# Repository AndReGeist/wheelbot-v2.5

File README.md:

# wheelbot-v2.5

This repository contains all files required to build a Wheelbot v2.5.

Project page:  [https://sites.google.com/view/wheelbot/start](https://sites.google.com/view/wheelbot/start)

## [/CAD files](https://github.com/AndReGeist/wheelbot-v2.5/tree/main/CAD%20files)
Contains the CAD files of the Wheelbot v2.5 as stl-files.

3D printer used: Markforged Onyx One <br/>
Material: Onyx <br/>
Layer height: 0.2 mm <br/>
Use default settings for all else. <br/>
See the following links for tips on printing: <br/>
https://markforged.com/resources/learn/design-for-additive-manufacturing-plastics-composites/3d-printing-strategies-for-composites/composites-3d-printing-design-tips <br/>
https://static.markforged.com/downloads/CompositesDesignGuide.pdf

The folder also contains the technical drawing for the cut copper rings forming the reaction wheel and the pdf *"wheelbot v2.5 assembly view.pdf"* that lets you interact with the complete Wheelbot's assembly (requires Adobe Acrobate reader).

## [/motherboard circuitry](https://github.com/AndReGeist/wheelbot-v2.5/tree/main/motherboard%20circuitry)
Contains the circuit layouts of the motherboard that connects to the Maevarm M2 and which also supplies the uDriver-v2 with power.

## [/simulation/matlab-symbolic-derivation-EOM](https://github.com/AndReGeist/wheelbot-v2.5/tree/main/simulation/matlab-symbolic-derivation-EOM)
Contains the matlab files used to symbolically derive the EOM of the Wheelbot.

**FlywUni_symbolic_derive.m:** Derives the Euler-Lagrange equations of a unicycle reaction wheel robot using the parameters set in "config_FlyUni" and the "Langrange.m" defined in external libraries.

**FlywUni_symbolic_linearize.m:** Reshapes the symbolic ODE obtained from "FlywUni_symbolic_derive", brings it into the form for the standard matlab ODE solvers and saves it as 
```matlab
save('EQS_matrices_nonlin.mat', 'M_nonlin', 'RHS_nonlin')
```
Also linearizes the set of equations and saves the linearization as 
```matlab
save('EQS_matrices.mat', 'M', 'RHS')
```

**FlywUni_symbolic_analyze.m:** Loads the pre-computed dynamic equations, computes a trajectory using a standard ODE solver (RK45), and plots trajectory and total energy of the system.

## [/simulation/simulink-model](https://github.com/AndReGeist/wheelbot-v2.5/tree/main/simulation/simulink-model)
Contains the simulink model used to tune the estimator and LQR controller. Recommended matlab version is R2020a.

The file *"s00_config"* contains the simulation settings including the exact estimates for the mass and inertia of the Wheelbot v2.5 which we obtained from CAD.

Before running *"s01_unicycle.slx"*, you need to run *"s00_designLQR"*.

## [/firmware](https://github.com/AndReGeist/wheelbot-v2.5/tree/main/firmware)
Contains the firmware required to run Wheelbot v2.5

### /firmware/M2-on-wheelbot
Contains the firmware that runs on a Maevarm M2 that is attached to the motherboard of the Wheelbot.

### /firmware/M2-wifi-dongle
Contains the firmware that runs on a Maevarm M2 being connected to a PC and that handles the wifi communication with the Wheelbot.

### /firmware/computer-python-interface
Python program running on Ubuntu 18.04 LTS collecting incoming data/outgoing commands from/to the wifi dongle.

# Erratum
In the initial publication, in Equation (3), the transform from averaged body rates ${}^{\text{B}}\omega_i$ to Euler rates was incorrectly denoted as

```math
\begin{bmatrix}
\dot{q}_{1, \mathrm{G}} \\
\dot{q}_{2, \mathrm{G}} \\
\dot{q}_{3, \mathrm{G}}
\end{bmatrix} = \begin{bmatrix}
e_1^{\mathrm{T}} R_2 \\
e_2^{\mathrm{T}} \\
e_3^{\mathrm{T}} R_1 R_2
\end{bmatrix} \sum_{k=1}^4 \frac{{ }^B \omega_i(k)}{4},
```

corresponding to

```math
\left[\begin{array}{c}
\dot{q}_{1, \mathrm{G}} \\
\dot{q}_{2, \mathrm{G}} \\
\dot{q}_{3, \mathrm{G}}
\end{array}\right]=\left[\begin{array}{c}
R_2^T e_1 &
e_2 &
R_2^T R_1^T e_3
\end{array}\right]^{\top} \sum_{i=1}^4 \frac{{ }^B \omega_i(k)}{4}.
```

However, the correct transform from averaged body rates ${}^{\text{B}}\omega_i$ to Euler rates is

```math
\left[\begin{array}{c}
\dot{q}_{1, \mathrm{G}} \\
\dot{q}_{2, \mathrm{G}} \\
\dot{q}_{3, \mathrm{G}}
\end{array}\right]=\left[\begin{array}{c}
R_2^T e_1 &
e_2 &
R_2^T R_1^T e_3
\end{array}\right]^{-1} \sum_{i=1}^4 \frac{{ }^B \omega_i(k)}{4}.
```

While we implemented the faulty transform in the Wheelbot's state estimation routine (see [main.c](https://github.com/AndReGeist/wheelbot-v2.5/blob/main/firmware/M2-on-wheelbot/src/main.c), Line 340),  the error had not been noticed during experimentation as the robot remained close to its upright equilibrium. In turn, $q_1$ and $q_2$ remained near zero such that both transforms became almost identical, as

```math
\left[\begin{array}{c}
R_2^T e_1 &
e_2 &
R_2^T R_1^T e_3
\end{array}\right]^{\top} =  \left[\begin{array}{c}
\cos(q_2) & 0 & \sin(q_2) \\
0 & 1 & 0 \\
-\cos(q_1) \sin(q_2) & \sin(q_1) & \cos(q_1) \cos(q_2)
\end{array}\right],
```

```math
\left[\begin{array}{c}
R_2^T e_1 &
e_2 &
R_2^T R_1^T e_3
\end{array}\right]^{-1} = \left[\begin{array}{c}
 \cos(q_2) & 0 & \sin(q_2) \\
 \tan(q_1) \sin(q_2) & 1 & -\tan(q_1) \cos(q_2) \\ 
 -\sin(q_2) / \cos(q_1) & 0 & \cos(q_2) / \cos(q_1)
\end{array}\right].
```

Importantly, **our results on tilt estimation using accelerometers** as depicted in Figure 10 **are not affected by this error**. In the first experiment (Figure 10, left) the robot's tilt angles were kept at zero. In the second experiment (Figure 10, right), $q_1 \approx 0$ such that $\tan(q_1) \approx q_1$. In turn, both transforms deviated only marginally from each other in both experiments.

We added a [Jupyter notebook](https://github.com/AndReGeist/wheelbot-v2.5/blob/main/erratum_bodyrate_transform.ipynb) to the projects Github repository detailing the calculation of the transform from body rates to Euler rates.

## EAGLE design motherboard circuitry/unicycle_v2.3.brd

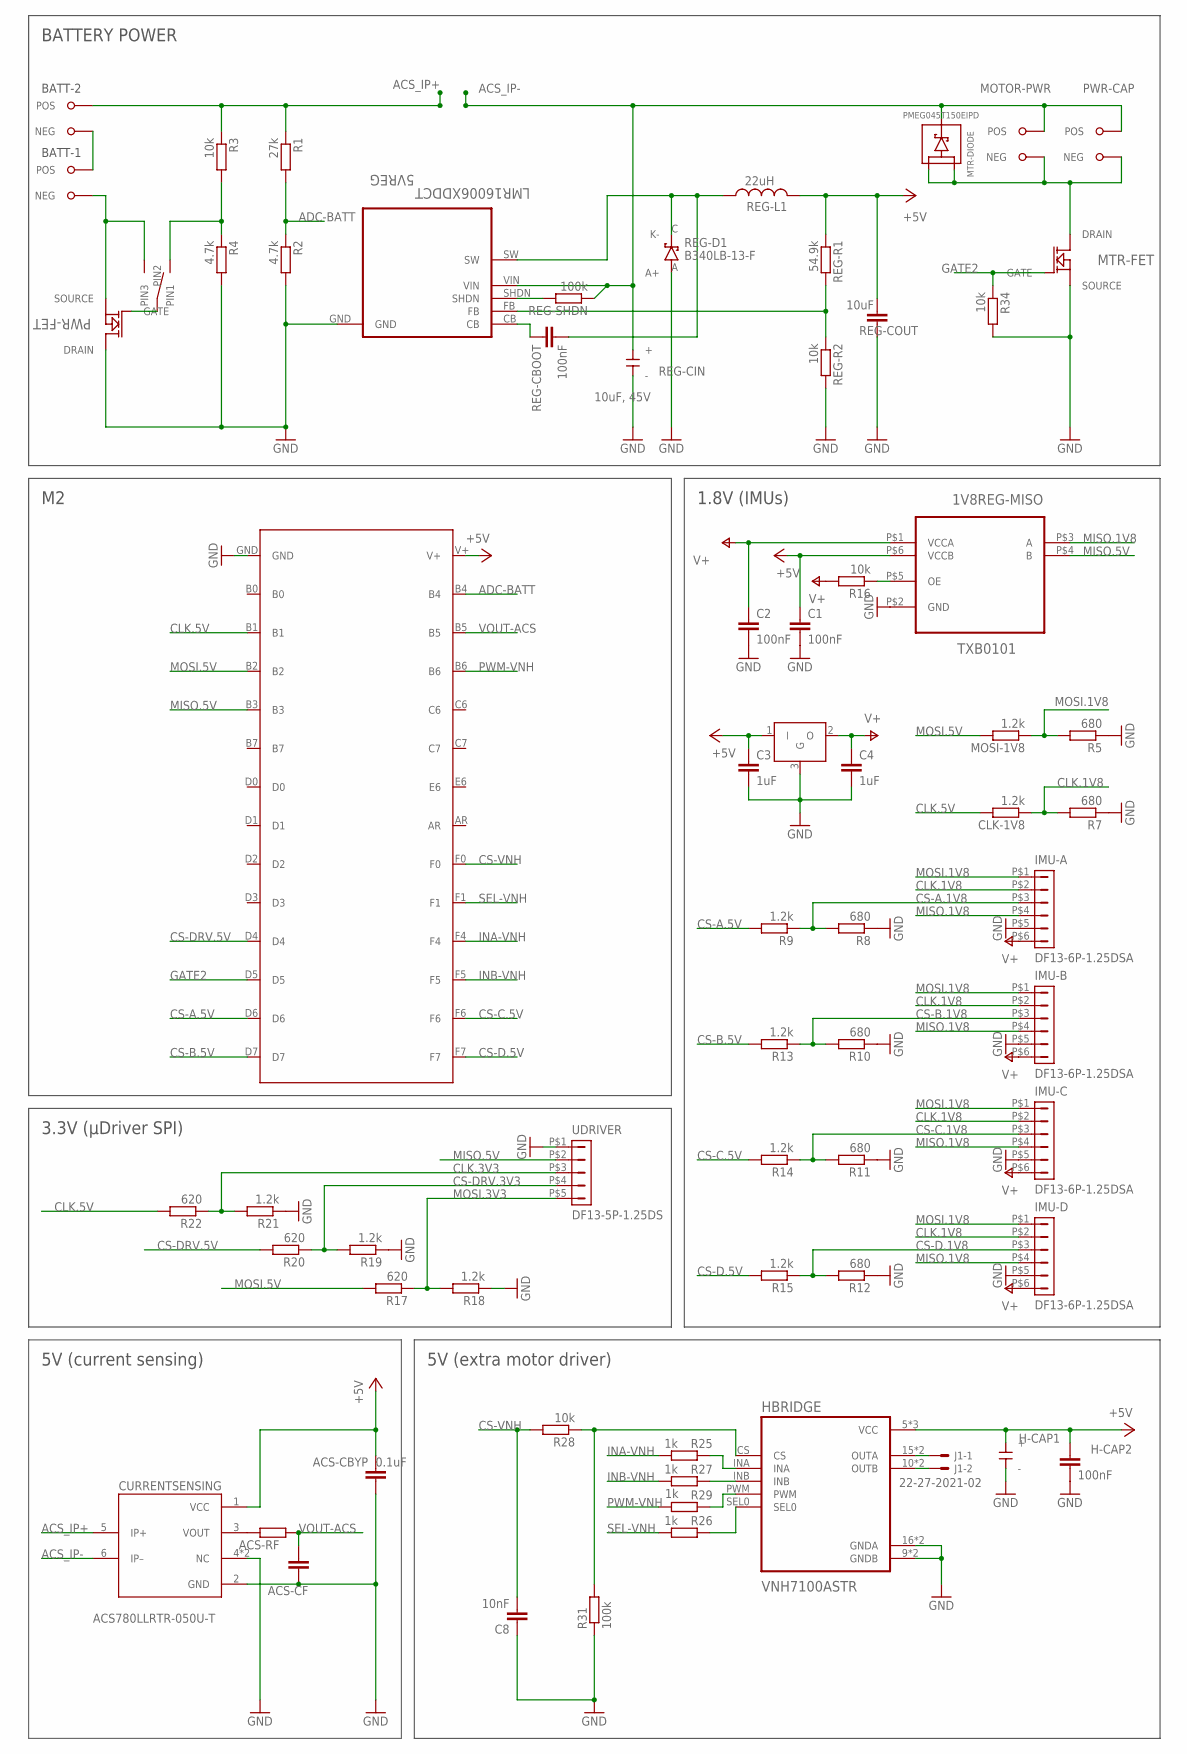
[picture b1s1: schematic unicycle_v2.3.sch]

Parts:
1V8-REG: AP7333AG; SOT23
1V8REG-MISO: TXB0101; SOT23-6
5VREG: LMR16006XDDCT; SOT95P280X110-6N
ACS-CBYP: 0.1uF; C0603
ACS-CF: C-EUC0603; C0603
ACS-RF: R-EU_R0603; R0603
C1, C2: 100nF; C0402
C3, C4: 1uF; C0402
C8: 10nF; C0402
CLK-1V8: 1.2k; R0402
CURRENTSENSING: ACS780LLRTR-050U-T; XDCR_ACS780LLRTR-050B-T
H-CAP1: TPSD337K006R0045; AVX_TPS-D
H-CAP2: 100nF; C0402
HBRIDGE: VNH7100ASTR; SOIC127P600X175-16N
IMU-A: DF13-6P-1.25DSA
IMU-B: DF13-6P-1.25DSA
IMU-C: DF13-6P-1.25DSA
IMU-D: DF13-6P-1.25DSA
J1: 22-27-2021-02; 6410-02
MOSI-1V8: 1.2k; R0402
MOTOR-PWR: 21AWG_X2
MTR-DIODE: PMEG045T150EIPD
MTR-FET: CSD18540Q5BT; DNK0008A
PWR-CAP: 21AWG_X2
PWR-FET: CSD18540Q5BT; DNK0008A
R1: 27k; R0402
R2, R4: 4.7k; R0402
R3, R16, R28, R34: 10k; R0402
R5, R7, R8, R10, R11, R12: 680; R0402
R9, R13, R14, R15, R18, R19, R21: 1.2k; R0402
R17, R20, R22: 620; R0402
R25, R26, R27, R29: 1k; R0402
R31: 100k; R0402
REG-CBOOT: 100nF; C0402
REG-CIN: 10uF, 45V; TCJD106M050R0120
REG-COUT: 10uF; C0603
REG-D1: B340LB-13-F; DIODES-SMB
REG-L1: 22uH; 4020
REG-R1: 54.9k; R0402
REG-R2: 10k; R0402
REG-SHDN: 100k; R0402
SWITCH: ATE1D-2M3-10-Z
U$2: M2; M1
U$8, U$9: XT30PW-M; XT30PW-M-NOHOLE
UDRIVER: DF13-5P-1.25DS

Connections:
+5V: 1V8-REG.1 (I), 1V8REG-MISO.P$6 (VCCB), ACS-CBYP.2, C1.1, C3.1, CURRENTSENSING.1 (VCC), H-CAP1.POS (+), H-CAP2.1, HBRIDGE.5 (VCC), HBRIDGE.12 (VCC), HBRIDGE.VCC, REG-COUT.1, REG-L1.P$2 (2), REG-R1.1, U$2.V+
ACS_IP+: CURRENTSENSING.5 (IP+), R1.1, R3.1, U$8.POS
ACS_IP-: 5VREG.VIN, CURRENTSENSING.6 (IP–), MOTOR-PWR.POS, MTR-DIODE.3 (K), PWR-CAP.POS, REG-CIN.POS (+), REG-SHDN.1
ADC-BATT: R1.2, R2.1, U$2.B4
CLK.1V8: CLK-1V8.1, IMU-A.P$2 (2), IMU-B.P$2 (2), IMU-C.P$2 (2), IMU-D.P$2 (2), R7.2
CLK.3V3: R21.2, R22.1, UDRIVER.P$3 (3)
CLK.5V: CLK-1V8.2, R22.2, U$2.B1
CS-A.1V8: IMU-A.P$3 (3), R8.2, R9.1
CS-A.5V: R9.2, U$2.D6
CS-B.1V8: IMU-B.P$3 (3), R10.2, R13.1
CS-B.5V: R13.2, U$2.D7
CS-C.1V8: IMU-C.P$3 (3), R11.2, R14.1
CS-C.5V: R14.2, U$2.F6
CS-D.1V8: IMU-D.P$3 (3), R12.2, R15.1
CS-D.5V: R15.2, U$2.F7
CS-DRV.3V3: R19.2, R20.1, UDRIVER.P$4 (4)
CS-DRV.5V: R20.2, U$2.D4
CS-VNH: C8.2, R28.2, U$2.F0
GATE2: MTR-FET.4 (GATE), R34.1, U$2.D5
GND: 1V8-REG.3 (G), 1V8REG-MISO.P$2 (GND), 5VREG.GND, ACS-CBYP.1, ACS-CF.2, C1.2, C2.2, C3.2, C4.2, C8.1, CURRENTSENSING.2 (GND), CURRENTSENSING.4 (NC), CURRENTSENSING.7 (NC), H-CAP1.NEG (-), H-CAP2.2, HBRIDGE.9 (GNDB), HBRIDGE.16 (GNDA), HBRIDGE.GNDA, HBRIDGE.GNDB, IMU-A.P$5 (5), IMU-B.P$5 (5), IMU-C.P$5 (5), IMU-D.P$5 (5), MTR-FET.1 (SOURCE), MTR-FET.2 (SOURCE), MTR-FET.3 (SOURCE), PWR-FET.9 (DRAIN), R2.2, R4.2, R5.1, R7.1, R8.1, R10.1, R11.1, R12.1, R18.1, R19.1, R21.1, R31.1, R34.2, REG-CIN.NEG (-), REG-COUT.2, REG-D1.A (A+), REG-R2.2, U$2.GND, UDRIVER.P$1 (1)
INA-VNH: R25.2, U$2.F4
INB-VNH: R27.2, U$2.F5
MISO.1V8: 1V8REG-MISO.P$3 (A), IMU-A.P$4 (4), IMU-B.P$4 (4), IMU-C.P$4 (4), IMU-D.P$4 (4)
MISO.5V: 1V8REG-MISO.P$4 (B), U$2.B3, UDRIVER.P$2 (2)
MOSI.1V8: IMU-A.P$1 (1), IMU-B.P$1 (1), IMU-C.P$1 (1), IMU-D.P$1 (1), MOSI-1V8.1, R5.2
MOSI.3V3: R17.1, R18.2, UDRIVER.P$5 (5)
MOSI.5V: MOSI-1V8.2, R17.2, U$2.B2
unnamed: 5VREG.SHDN, REG-SHDN.2
unnamed: HBRIDGE.15 (OUTA), HBRIDGE.OUTA, J1.1
unnamed: MOTOR-PWR.NEG, MTR-DIODE.1 (A1), MTR-DIODE.2 (A2), MTR-FET.9 (DRAIN), PWR-CAP.NEG
unnamed: 5VREG.FB, REG-R1.2, REG-R2.1
unnamed: 5VREG.SW, REG-CBOOT.1, REG-D1.C (K-), REG-L1.P$1 (1)
unnamed: 5VREG.CB, REG-CBOOT.2
unnamed: 1V8REG-MISO.P$5 (OE), R16.1
unnamed: U$8.NEG, U$9.POS
unnamed: PWR-FET.1 (SOURCE), PWR-FET.2 (SOURCE), PWR-FET.3 (SOURCE), SWITCH.P$3 (PIN3), U$9.NEG
unnamed: R3.2, R4.1, SWITCH.P$1 (PIN1)
unnamed: HBRIDGE.INB, R27.1
unnamed: HBRIDGE.SEL0, R26.1
unnamed: HBRIDGE.PWM, R29.1
unnamed: PWR-FET.4 (GATE), SWITCH.P$2 (PIN2)
unnamed: HBRIDGE.CS, R28.1, R31.2
unnamed: ACS-RF.2, CURRENTSENSING.3 (VOUT)
unnamed: HBRIDGE.10 (OUTB), HBRIDGE.OUTB, J1.2
unnamed: HBRIDGE.INA, R25.1
PWM-VNH: R29.2, U$2.B6
SEL-VNH: R26.2, U$2.F1
V+: 1V8-REG.2 (O), 1V8REG-MISO.P$1 (VCCA), C2.1, C4.1, IMU-A.P$6 (6), IMU-B.P$6 (6), IMU-C.P$6 (6), IMU-D.P$6 (6), R16.2
VOUT-ACS: ACS-CF.1, ACS-RF.1, U$2.B5

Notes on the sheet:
BATT-1
BATT-2
3.3V (µDriver SPI)
1.8V (IMUs)
BATTERY POWER
5V (extra motor driver)
5V (current sensing)

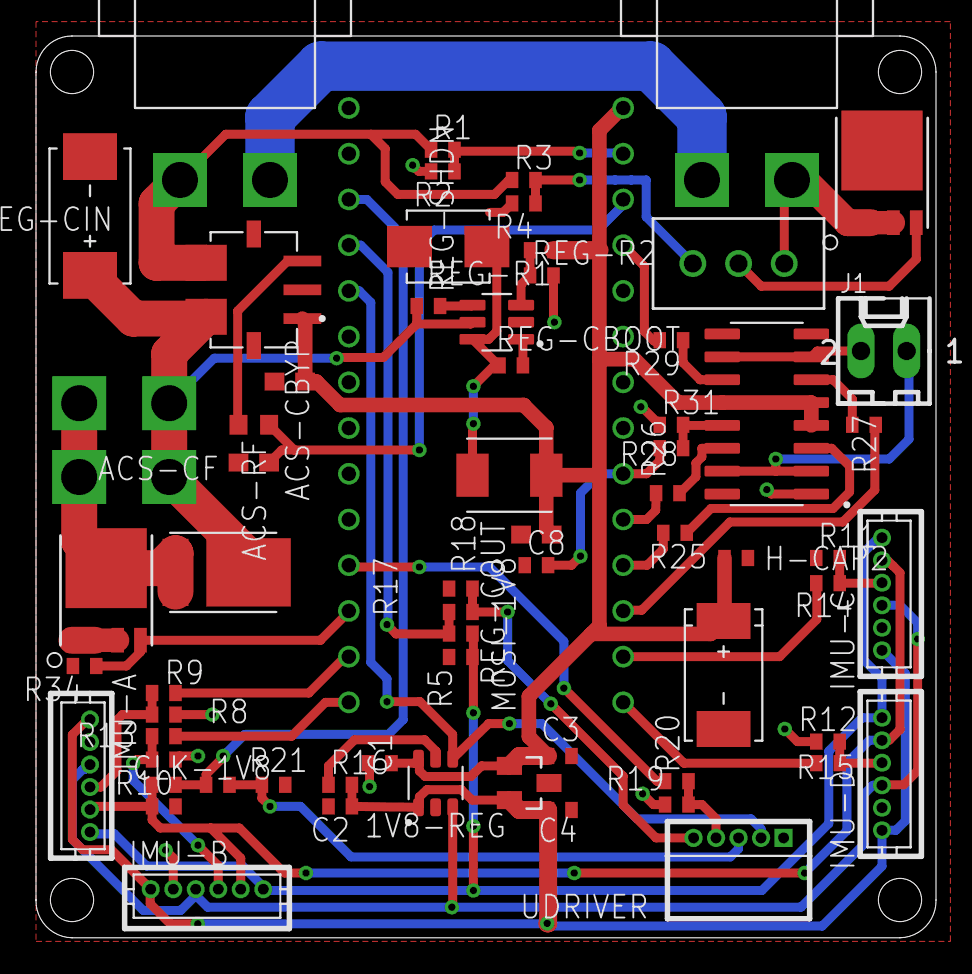
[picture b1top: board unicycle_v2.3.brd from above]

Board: 2 copper layers, 50.0 x 50.1 mm, 68 parts (0 on the bottom side), 49 nets.

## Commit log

2022-06-03 Added motherboard circuit layouts
2022-06-03 Added CAD files (stl format) of wheelbot v2.5
2022-06-03 Added pdf file of assembled robot
2022-06-03 Added firmware used to run the robot
2022-06-03 Added juypter notebook used to estimate the robot dimensions
2022-06-03 Added simulink model
2022-06-03 Added symbolic derivation of the nonlinear dynamics that are used in the simulink model
2022-06-03 Added readme
2023-07-23 Added notebook detailing transform from body- to euler rates
2023-07-23 Added erratum concerning body rate transform
2023-07-23 Fixed formatting in erratum concerning body rate transform
2023-07-23 Fixed typo
